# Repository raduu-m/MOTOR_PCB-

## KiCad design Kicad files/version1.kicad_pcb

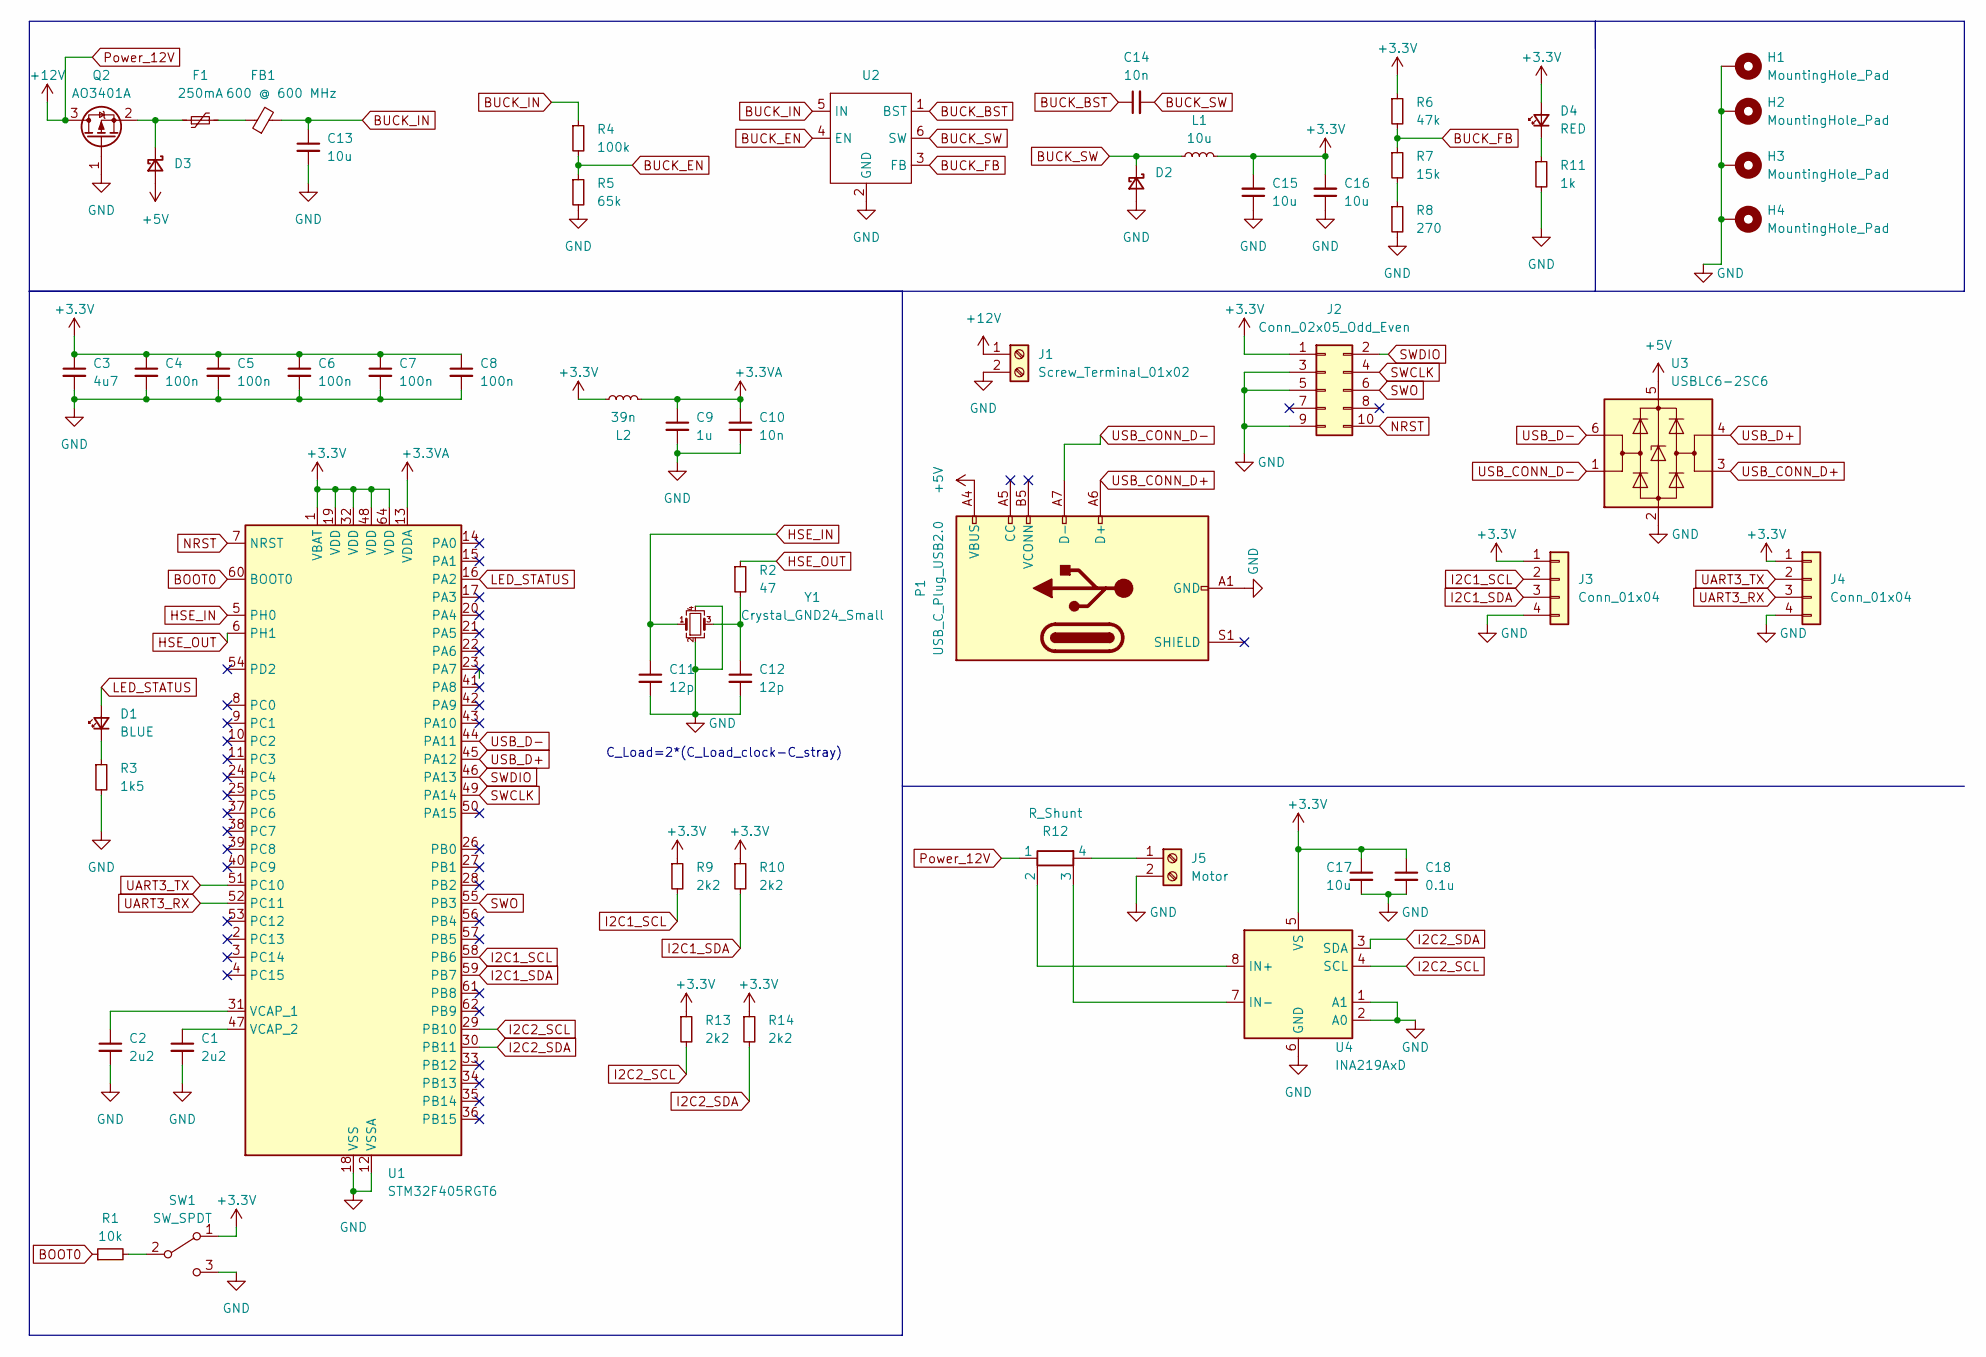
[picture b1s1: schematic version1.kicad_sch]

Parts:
C1, C2: 2u2; C_0603_1608Metric
C3: 4u7; C_0402_1005Metric
C4, C5, C6, C7, C8: 100n; C_0402_1005Metric
C9: 1u; C_0402_1005Metric
C10: 10n; C_0402_1005Metric
C11, C12: 12p; C_0402_1005Metric
C13, C15, C16: 10u; C_1206_3216Metric
C14: 10n; C_0603_1608Metric
C17: 10u; C_0402_1005Metric
C18: 0.1u; C_0402_1005Metric
D1: BLUE; LED_0603_1608Metric
D2, D3: D_Schottky_Small; D_SOD-123
D4: RED; LED_0603_1608Metric
F1: 250mA; Fuse_1206_3216Metric
FB1: 600 @ 600 MHz; L_0805_2012Metric
H1, H2, H3, H4: MountingHole_Pad; MountingHole_3.2mm_M3_DIN965_Pad
J1: Screw_Terminal_01x02; TerminalBlock_Phoenix_PT-1,5-2-3.5-H_1x02_P3.50mm_Horizontal
J2: Conn_02x05_Odd_Even; PinSocket_2x05_P1.27mm_Vertical_SMD
J3, J4: Conn_01x04; Molex_PicoBlade_53048-0410_1x04_P1.25mm_Horizontal
J5: Motor; TerminalBlock_Phoenix_PT-1,5-2-3.5-H_1x02_P3.50mm_Horizontal
L1: 10u; L_Sunlord_MWSA0518S
L2: 39n; L_0402_1005Metric
P1: USB_C_Plug_USB2.0; USB_C_Plug_ShenzhenJingTuoJin_918-118A2021Y40002_Vertical
Q2: AO3401A; SOT-23
R1: 10k; R_0402_1005Metric
R2: 47; R_0402_1005Metric
R3: 1k5; R_0603_1608Metric
R4: 100k; R_0603_1608Metric
R5: 65k; R_0603_1608Metric
R6: 47k; R_0603_1608Metric
R7: 15k; R_0603_1608Metric
R8: 270; R_0603_1608Metric
R9, R10, R13, R14: 2k2; R_0402_1005Metric
R11: 1k; R_0603_1608Metric
R12: R_Shunt; R_Shunt_Ohmite_LVK12
SW1: SW_SPDT; SW_SPDT_PCM12
U1: STM32F405RGT6; LQFP-64_10x10mm_P0.5mm
U2: SOT-23-6
U3: USBLC6-2SC6; SOT-23-6
U4: INA219AxD; SOIC-8_3.9x4.9mm_P1.27mm
Y1: Crystal_GND24_Small; Crystal_SMD_3225-4Pin_3.2x2.5mm

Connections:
+3.3V: C3.1, C4.1, C5.1, C6.1, C7.1, C8.1, C15.2, C16.2, C17.1, C18.1, D4.2 (A), J2.1, J3.1, J4.1, L1.2, L2.2, R6.1, R9.1, R10.1, R13.1, R14.1, SW1.1 (A), U1.1 (VBAT), U1.19 (VDD), U1.32 (VDD), U1.48 (VDD), U1.64 (VDD), U4.5 (VS)
+3.3VA: C9.1, C10.1, L2.1, U1.13 (VDDA)
+5V: D3.2 (A), P1.A4 (VBUS), P1.A9 (VBUS), P1.B4 (VBUS), P1.B9 (VBUS), U3.5 (VBUS)
BOOT0: R1.1, U1.60 (BOOT0)
BUCK_BST: C14.1, U2.1 (BST)
BUCK_EN: R4.2, R5.1, U2.4 (EN)
BUCK_FB: R6.2, R7.1, U2.3 (FB)
BUCK_IN: C13.1, FB1.2, R4.1, U2.5 (IN)
BUCK_SW: C14.2, D2.1 (K), L1.1, U2.6 (SW)
GND: C1.2, C2.2, C3.2, C4.2, C5.2, C6.2, C7.2, C8.2, C9.2, C10.2, C11.2, C12.2, C13.2, C15.1, C16.1, C17.2, C18.2, D2.2 (A), H1.1, H2.1, H3.1, H4.1, J1.2, J2.3, J2.5, J2.9, J3.4, J4.4, J5.2, P1.A1 (GND), P1.A12 (GND), P1.B1 (GND), P1.B12 (GND), Q2.1 (G), R3.2, R5.2, R8.2, R11.2, SW1.3 (C), U1.12 (VSSA), U1.18 (VSS), U1.63 (VSS), U2.2 (GND), U3.2 (GND), U4.1 (A1), U4.2 (A0), U4.6 (GND), Y1.2, Y1.4
HSE_IN: C11.1, U1.5 (PH0), Y1.1
HSE_OUT: R2.1, U1.6 (PH1)
I2C1_SCL: J3.2, R9.2, U1.58 (PB6)
I2C1_SDA: J3.3, R10.2, U1.59 (PB7)
I2C2_SCL: R13.2, U1.29 (PB10), U4.4 (SCL)
I2C2_SDA: R14.2, U1.30 (PB11), U4.3 (SDA)
LED_STATUS: D1.2 (A), U1.16 (PA2)
NRST: J2.10, U1.7 (NRST)
unnamed: C12.1, R2.2, Y1.3
unnamed: D1.1 (K), R3.1
unnamed: D3.1 (K), F1.1, Q2.2 (S)
unnamed: D4.1 (K), R11.1
unnamed: F1.2, FB1.1
unnamed: J5.1, R12.4
unnamed: R7.2, R8.1
unnamed: R1.2, SW1.2 (B)
unnamed: C2.1, U1.31 (VCAP_1)
unnamed: C1.1, U1.47 (VCAP_2)
unnamed: R12.2, U4.8 (IN+)
unnamed: R12.3, U4.7 (IN-)
Power_12V: J1.1, Q2.3 (D), R12.1
SWCLK: J2.4, U1.49 (PA14)
SWDIO: J2.2, U1.46 (PA13)
SWO: J2.6, U1.55 (PB3)
UART3_RX: J4.3, U1.52 (PC11)
UART3_TX: J4.2, U1.51 (PC10)
USB_CONN_D+: P1.A6 (D+), U3.3 (I/O2)
USB_CONN_D-: P1.A7 (D-), U3.1 (I/O1)
USB_D+: U1.45 (PA12), U3.4 (I/O2)
USB_D-: U1.44 (PA11), U3.6 (I/O1)

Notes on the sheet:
C_Load=2*(C_Load_clock-C_stray)

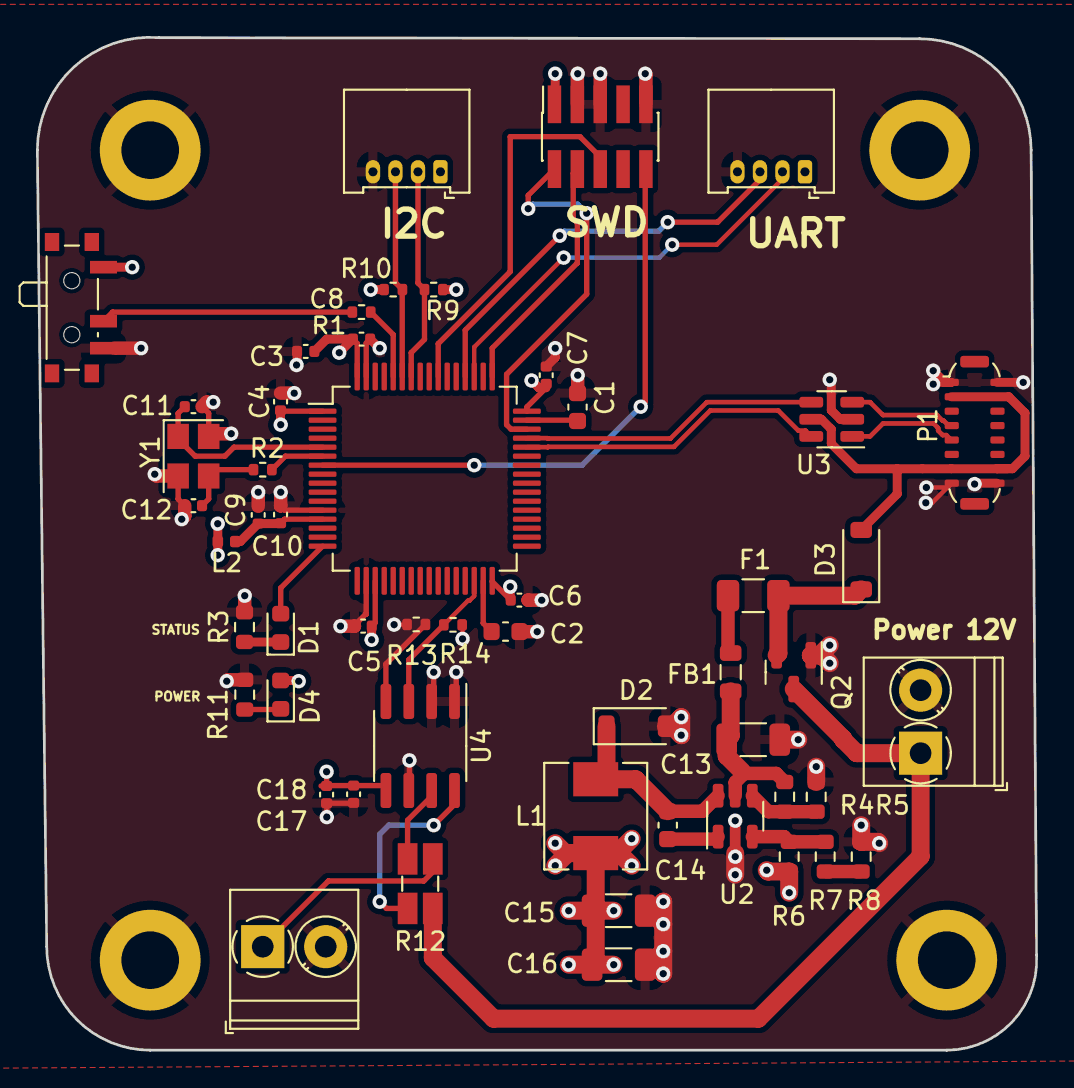
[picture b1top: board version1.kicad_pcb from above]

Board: 4 copper layers, 55.5 x 56.3 mm, 57 parts (0 on the bottom side), 40 nets.

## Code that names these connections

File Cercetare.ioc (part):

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Mcu.Name=STM32F405RGTx
Mcu.Package=LQFP64
Mcu.UserName=STM32F405RGTx
PA11.Mode=Device_Only
PA11.Signal=USB_OTG_FS_DM
PA12.Mode=Device_Only
PA12.Signal=USB_OTG_FS_DP
PA13.Mode=JTAG_4_pins
PA13.Signal=SYS_JTMS-SWDIO
PA14.Mode=JTAG_4_pins
PA14.Signal=SYS_JTCK-SWCLK
PA15.Mode=JTAG_4_pins
PA15.Signal=SYS_JTDI
PB10.Mode=I2C
PB10.Signal=I2C2_SCL
PB11.Mode=I2C
PB11.Signal=I2C2_SDA
PB3.Mode=JTAG_4_pins
PB3.Signal=SYS_JTDO-SWO
PB6.Mode=I2C
PB6.Signal=I2C1_SCL
PB7.Mode=I2C
PB7.Signal=I2C1_SDA
PC10.Mode=Asynchronous
PC10.Signal=USART3_TX
PC11.Mode=Asynchronous
PC11.Signal=USART3_RX
PH0-OSC_IN.Mode=HSE-External-Oscillator
PH0-OSC_IN.Signal=RCC_OSC_IN
PH1-OSC_OUT.Mode=HSE-External-Oscillator
PH1-OSC_OUT.Signal=RCC_OSC_OUT
RCC.HSE_VALUE=25000000
RCC.SYSCLKFreq_VALUE=120000000
RCC.SYSCLKSource=RCC_SYSCLKSOURCE_PLLCLK
board=custom

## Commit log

2024-01-17 Added kicad files
